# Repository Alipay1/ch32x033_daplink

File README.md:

# ch32x033_daplink
 daplink based on [ch32x033f8p6](https://github.com/ylj2000/DAPLink_X033)

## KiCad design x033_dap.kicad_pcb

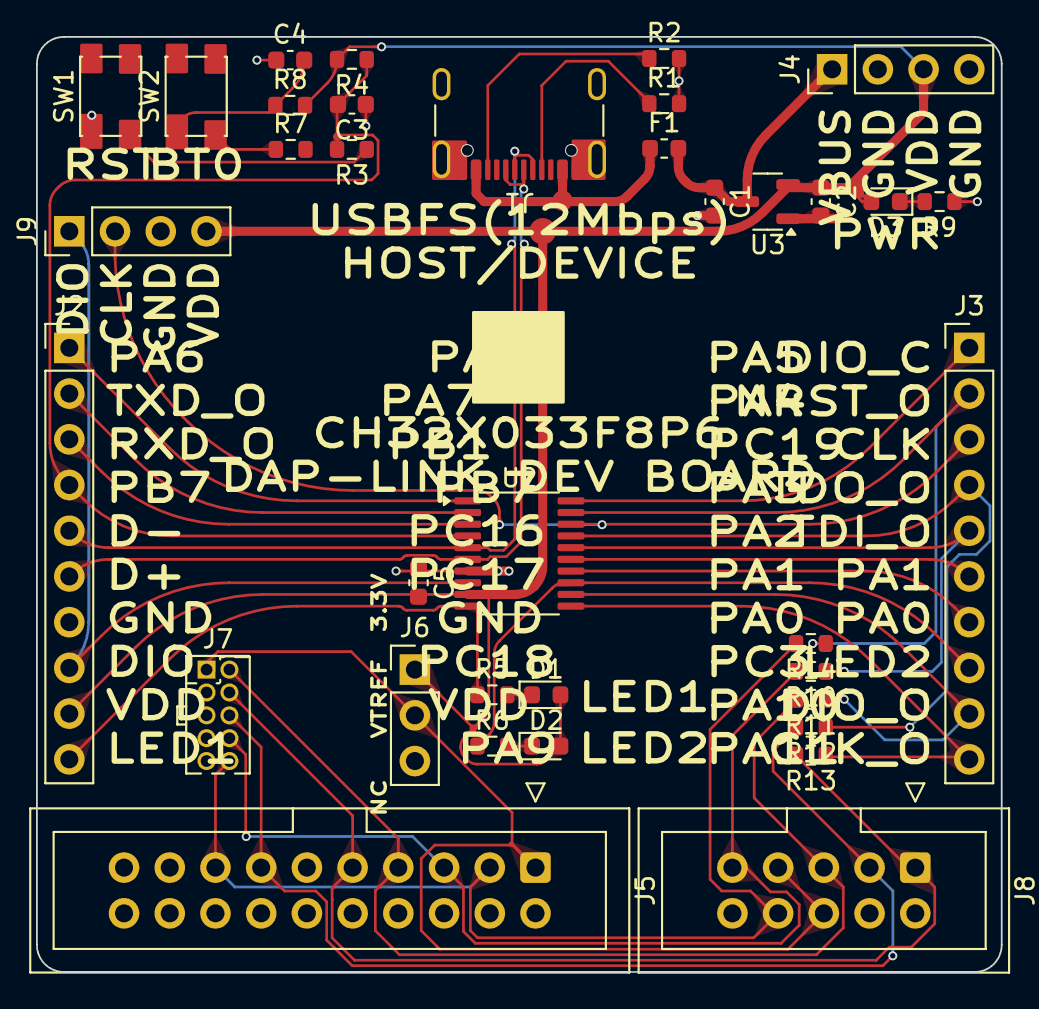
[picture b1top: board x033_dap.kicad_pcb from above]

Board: 2 copper layers, 53.6 x 52.0 mm, 36 parts (0 on the bottom side), 35 nets.

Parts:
C1, C2: 1uF; C_0603_1608Metric
C3, C4, C5: 100nF; C_0603_1608Metric
D1, D2, D3: LED; LED_0603_1608Metric
F1: 500mA; Fuse_0603_1608Metric
J1: USB_C_Receptacle_USB2.0_16P; USB_C_Receptacle_GCT_USB4105-xx-A_16P_TopMnt_Horizontal
J2, J3: Conn_01x10; PinHeader_1x10_P2.54mm_Vertical
J4, J9: Conn_01x04; PinHeader_1x04_P2.54mm_Vertical
J5: Conn_ARM_JTAG_SWD_20; IDC-Header_2x10_P2.54mm_Vertical
J6: Conn_01x03_Pin; PinHeader_1x03_P2.54mm_Vertical
J7: Conn_ARM_JTAG_SWD_10; PinHeader_2x05_P1.27mm_Vertical
J8: Microsemi_FlashPro-JTAG-10; IDC-Header_2x05_P2.54mm_Vertical
R1, R2, R5, R6, R9: 5.1k; R_0603_1608Metric
R3, R7: 1k; R_0603_1608Metric
R4, R8: 10k; R_0603_1608Metric
R10, R11, R12, R13, R14: 33R; R_0603_1608Metric
SW1, SW2: Push_Button; SW_SPST_PTS810
U2: CH32X033F8P6; TSSOP-20_4.4x6.5mm_P0.65mm
U3: XC6206PxxxMR; SOT-23-3

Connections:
/dap_link_x033/CLK: J3.3, J5.9 (TCK/SWCLK), J7.4 (SWCLK/TCK), J8.1 (TCK), J9.2, R13.2, U2.18 (PC19/DCK/T2C1_/T3C1_/I2C_/RX3_/C1P0)
/dap_link_x033/CLK_O: J3.10, R13.1, U2.11 (PA11/SDA/SCK_/RX1_/C2P1)
/dap_link_x033/D+: J1.A6 (D+), J1.B6 (D+), J2.6, R7.2, U2.6 (PC17/UDP/TX4_5/I2C_/RX4_2/T1ET/PC10)
/dap_link_x033/D-: J1.A7 (D-), J1.B7 (D-), J2.5, U2.5 (PC16/UDM/T1C4/TX4_2/I2C_/RX4_5/PC11)
/dap_link_x033/DIO: J2.8, J9.1, U2.8 (PC18/DIO/TX3_/T2C1N_/T3C2_/I2C_/T1ET_)
/dap_link_x033/DIO_C: J3.1, U2.20 (PA5/SCK/TX4_1/O2N0/A5)
/dap_link_x033/DIO_O: J3.9, R11.1, U2.12 (PA10/SCL/TX1_/MOSI_)
/dap_link_x033/DIO_OO: J5.7 (TMS/SWDIO), J7.2 (SWDIO/TMS), J8.5 (TMS), R11.2
/dap_link_x033/GND_DAP: C1.2, C2.2, C3.1, C4.1, C5.1, J1.A1 (GND), J1.A12 (GND), J1.B1 (GND), J1.B12 (GND), J1.S1 (SHIELD), J2.7, J4.2, J4.4, J5.4 (GND), J5.6 (GND), J5.8 (GND), J5.10 (GND), J5.12 (GND), J5.14 (GND), J5.16 (GND), J5.18 (GND), J5.20 (GND), J7.3 (GND), J7.5 (GND), J7.9 (GNDDetect), J8.2 (GND), J8.10 (GND), J9.3, R1.2, R2.2, R9.1, SW1.1, U2.7 (GND), U3.1 (GND)
/dap_link_x033/LED1: J2.10, R5.1, U2.10 (PA9/MISO_/RX4_1/T2BK_)
/dap_link_x033/LED2: J3.8, R6.1, U2.13 (PC3/T1C4_/T2C1N_/C1N0/C2N1/A13)
/dap_link_x033/NRST_O: J3.2, R14.1, U2.19 (PA4/CS/O2O0/T3C2_/A4)
/dap_link_x033/NRST_OO: J5.3 (~TRST), J5.15 (~SRST), J7.10 (~RESET), J8.8 (~TRST), R14.2
/dap_link_x033/PA0_RESERVE: J3.7, U2.14 (PA0/T2C1/C1P1/A0)
/dap_link_x033/PA1_RESERVE: J3.6, U2.15 (PA1/T2C2/C1O/O1N2/O2N2/A1)
/dap_link_x033/PA6_RESERVE: J2.1, U2.1 (PA6/MISO/T3C1/T1BK_/O1N0/A6)
/dap_link_x033/PB7_RESERVE: C3.2, J2.4, R3.2, R4.1, U2.4 (PB7/RST/T1C2N/O2P2)
/dap_link_x033/RXD_O: J2.3, U2.3 (PB1/T1C3N_/RX4/O2N1/A9)
/dap_link_x033/TDI_O: J3.5, R10.1, U2.16 (PA2/TX2/T2C3/O2O1/T2ET_/A2)
/dap_link_x033/TDI_OO: J5.5 (TDI), J7.8 (NC/TDI), J8.9 (TDI), R10.2
/dap_link_x033/TDO_O: J3.4, R12.1, U2.17 (PA3/T2C4/T3C1_/RX2/O1O0/A3)
/dap_link_x033/TDO_OO: J5.13 (TDO/SWO), J7.6 (SWO/TDO), J8.3 (TDO), R12.2
/dap_link_x033/TXD_O: J2.2, U2.2 (PA7/MOSI/T3C2/T1C1N_/O2P0/PB0/TX4/T1C2N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)
/dap_link_x033/VBUS_DAP: C1.1, F1.2, J4.1, U3.3 (VI)
/dap_link_x033/VBUS_IN: F1.1, J1.A4 (VBUS), J1.A9 (VBUS), J1.B4 (VBUS), J1.B9 (VBUS)
/dap_link_x033/VDD_DAP: C2.1, C5.2, D1.2 (A), D2.2 (A), D3.2 (A), J2.9, J4.3, J6.1, J9.4, R4.2, R8.2, U2.9 (VDD), U3.2 (VO)
/dap_link_x033/VTREF: J5.1 (VTREF), J6.2, J7.1 (VTref), J8.6 (VJTAG), J8.7 (VPUMP)
unnamed: C4.2, R8.1, SW2.1
unnamed: D1.1 (K), R5.2
unnamed: D2.1 (K), R6.2
unnamed: D3.1 (K), R9.2
unnamed: J1.A5 (CC1), R1.1
unnamed: J1.B5 (CC2), R2.1
unnamed: R3.1, SW1.2
unnamed: R7.1, SW2.2

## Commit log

2024-07-17 upload kicad files
